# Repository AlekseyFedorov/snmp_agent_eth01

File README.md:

# SNMP Agent на базе WT32-ETH01

Мониторинг серверного помещения по SNMP v2c: температура, протечка воды, открытие дверей, удалённая смена сетевых настроек.

## Возможности

- **Температура** — DS18B20 по 1-Wire, опрос каждые 2 секунды
- **Протечка воды** — Gidrolock WSP через транзисторную развязку
- **Датчики дверей** — 2 геркона (сухой контакт)
- **Светодиодная индикация** — сеть, авария
- **SNMP v2c** — стандартный MIB2 + кастомный enterprise MIB
- **Удалённая смена IP/шлюза/маски** — SNMP SET с валидацией и авто-перезагрузкой
- **Сброс к заводским** — удержание кнопки 5 секунд (стирает NVS)
- **Аппаратный watchdog** — автоматическая перезагрузка при зависании задач

## Список компонентов (BOM)

| Компонент | Количество | Примечание |
|-----------|-----------|------------|
| WT32-ETH01 | 1 | ESP32 + LAN8720 Ethernet |
| DS18B20 | 1 | Датчик температуры, 1-Wire, TO-92 |
| Gidrolock WSP | 1 | Двухпроводный датчик протечки |
| Геркон (магнитоконтактный) | 2 | NO, сухой контакт, для дверей |
| Транзистор NPN 2N3904 | 1 | Развязка датчика протечки |
| Резистор 4.7 кОм | 1 | Подтяжка DS18B20 (VDD ↔ DQ) |
| Резистор 10 кОм | 2 | База транзистора + стягивание базы к GND |
| Резистор 330 Ом | 2 | Токоограничение светодиодов |
| Светодиод зелёный | 1 | Индикатор «Сеть» |
| Светодиод красный | 1 | Индикатор «Авария» |
| Кнопка тактовая | 1 | Сброс настроек (GPIO 5) |
| Блок питания 5V | 1 | Питание платы и датчиков |
| Макетная плата + провода | — | Для сборки |

## Распиновка

| GPIO | Функция | Режим | Примечание |
|------|---------|-------|------------|
| 32 | DS18B20 DQ | INPUT | 1-Wire данные, pull-up 4.7кОм к 3.3V |
| 33 | Gidrolock WSP | INPUT_PULLUP | Через NPN-транзистор (2N3904) |
| 14 | Дверь 1 | INPUT_PULLUP | Геркон: замкнут на GND = закрыта |
| 15 | Дверь 2 | INPUT_PULLUP | Геркон: замкнут на GND = закрыта |
| 2 | LED Сеть | OUTPUT | Через резистор 330Ω |
| 4 | LED Авария | OUTPUT | Через резистор 330Ω |
| 5 | Кнопка сброса | INPUT_PULLUP | Удержание 5 сек = factory reset |
| 16 | CLK 50MHz | OUTPUT | Внешний осциллятор для LAN8720 |

## Логика работы датчиков

### DS18B20 (температура)

Питание 3.3V, данные по 1-Wire на GPIO 32. Между VDD и DQ обязателен резистор 4.7 кОм. Значение публикуется в SNMP как `INTEGER` (температура × 10).

### Gidrolock WSP (протечка)

Датчик питается от 5V. Без воды — ток не течёт, база транзистора (2N3904) притянута к GND резистором 10 кОм, транзистор закрыт, на GPIO 33 — логическая 1 (PULLUP). При протечке вода замыкает контакты, ток через резистор базы 10 кОм открывает транзистор, GPIO замыкается на GND — логический 0.

> [!CAUTION]
> Никогда не подключайте Gidrolock WSP напрямую к GPIO! Напряжение шлейфа 5–24V сожжёт порт. Только через транзистор.

### Герконы (двери)

Дверь закрыта: магнит рядом, геркон замкнут, GPIO → GND = 0. Дверь открыта: геркон разомкнут, GPIO → PULLUP = 1. SNMP возвращает 1 при открытии (тревога).

## Сборка и прошивка

### Требования

- ESP-IDF v5.0+ (протестировано на v6.0.1)
- LWIP с поддержкой SNMP (включается автоматически через компонент `snmp_lwip`)

### Порядок сборки

```bash
git clone https://github.com/AlekseyFedorov/snmp2_agent_eth01.git
cd snmp2_agent_eth01

idf.py set-target esp32
idf.py build
idf.py -p COM3 flash monitor
```

### Заводские параметры

| Параметр | Значение |
|----------|---------|
| IP-адрес | 10.149.130.75 |
| Шлюз | 10.149.130.65 |
| Маска | 255.255.255.224 |
| Flash | 8 MB |
| SNMP Read Community | public |
| SNMP Write Community | private |

> Параметры хранятся в `main/ethernet_app.c` и NVS. После первого запуска сохраняются в NVS. При изменении через SNMP SET устройство перезагружается.

## Структура проекта

```
snmp2_agent_eth01/
├── CMakeLists.txt
├── sdkconfig
├── sdkconfig.defaults
├── dependencies.lock
├── main/
│   ├── CMakeLists.txt
│   ├── idf_component.yml
│   ├── main.c              # SNMP-агент, дерево MIB, задачи FreeRTOS
│   ├── ethernet_app.c/h    # Инициализация Ethernet, статический IP
│   ├── sensors_app.c/h     # Драйверы датчиков (DS18B20, протечка, герконы)
│   └── led_app.c/h         # Светодиодная индикация
└── components/
    └── snmp_lwip/
        ├── CMakeLists.txt   # Сборка SNMP-исходников lwip
        └── idf_component.yml
```

Примечание: SNMP-исходники lwip собираются отдельным компонентом `snmp_lwip`, поскольку в IDF v6 опция `LWIP_SNMP` исключена из Kconfig.

## SNMP-команды

Базовый OID: `.1.3.6.1.4.1.9999.1`

### Чтение (GET)

```bash
# Температура (×10°C)
snmpget -v 2c -c public <IP> .1.3.6.1.4.1.9999.1.1.0

# Протечка (0 — сухо, 1 — тревога)
snmpget -v 2c -c public <IP> .1.3.6.1.4.1.9999.1.6.0

# Дверь 1 (0 — закрыта, 1 — открыта)
snmpget -v 2c -c public <IP> .1.3.6.1.4.1.9999.1.7.0

# Дверь 2
snmpget -v 2c -c public <IP> .1.3.6.1.4.1.9999.1.8.0

# Пройти всё дерево
snmpwalk -v 2c -c public <IP> .1.3.6.1.4.1.9999.1
```

### Запись (SET)

```bash
# Изменение IP/шлюза/маски (одним пакетом):
snmpset -v 2c -c private <IP> \
  .1.3.6.1.4.1.9999.1.10.0 s "10.149.130.80" \
  .1.3.6.1.4.1.9999.1.11.0 s "10.149.130.65" \
  .1.3.6.1.4.1.9999.1.12.0 s "255.255.255.224"
```

После записи устройство перезагрузится через 1 секунду.

### OID-карта

| OID | Тип | Доступ | Описание |
|-----|-----|--------|----------|
| .1.0 | INTEGER | RO | Температура ×10°C |
| .2.0 | GAUGE32 | RO | Свободная heap-память (байт) |
| .3.0 | TIMETICKS | RO | Uptime (×10 мс) |
| .4.0 | GAUGE32 | RO | Использовано heap, % |
| .5.0 | OCTET STRING | RO | MAC-адрес (6 байт) |
| .6.0 | INTEGER | RO | Протечка воды (0 — сухо, 1 — тревога) |
| .7.0 | INTEGER | RO | Дверь 1 (0 — закрыта, 1 — открыта) |
| .8.0 | INTEGER | RO | Дверь 2 (0 — закрыта, 1 — открыта) |
| .10.0 | OCTET STRING | RW | IP-адрес |
| .11.0 | OCTET STRING | RW | Шлюз |
| .12.0 | OCTET STRING | RW | Маска подсети |

## Индикация

| Светодиод | GPIO | Логика |
|-----------|------|--------|
| LED Сеть (зелёный) | IO2 | Горит — сеть активна; мигает — нет линка |
| LED Авария (красный) | IO4 | Мигает при: протечке, открытой двери, t > 45°C |

## Сброс к заводским настройкам

Удержание кнопки на GPIO 5 в течение 5 секунд стирает NVS-раздел. После перезагрузки устройство стартует с параметрами по умолчанию из `ethernet_app.c`.

## Возможные улучшения

- **DHT22 / BME280** — датчик влажности и давления для полного климат-контроля
- **Оптрон PC817** — гальваническая развязка датчика протечки вместо транзистора
- **SNMP Trap** — активная отправка уведомлений в NMS (Zabbix/PRTG) при авариях
- **mDNS** — авто-обнаружение устройства в сети (`snmp-agent.local`)

## Лицензия

MIT.

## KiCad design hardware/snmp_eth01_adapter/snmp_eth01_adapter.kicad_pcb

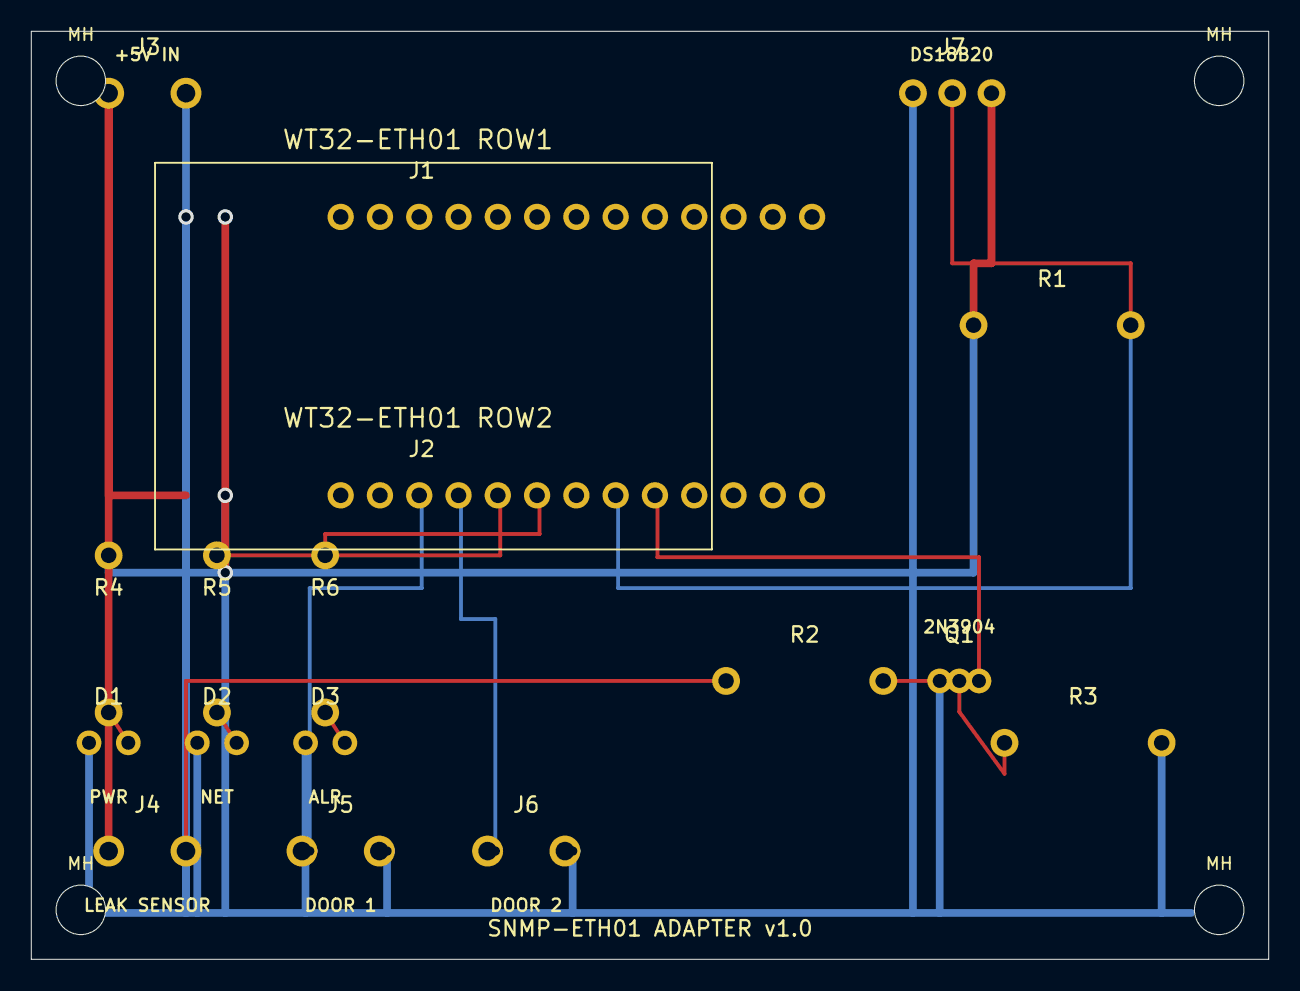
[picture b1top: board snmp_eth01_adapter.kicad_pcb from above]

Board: 2 copper layers, 80.0 x 60.0 mm, 21 parts (0 on the bottom side), 14 nets.

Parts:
D1: LED_PWR; D1
D2: LED_NET; D2
D3: LED_ALR; D3
J1: PinSocket_1x13_2.54mm; J1
J2: PinSocket_1x13_2.54mm; J2
J3: PWR_IN_5V; J3
J4: GIDROLOCK_WSP; J4
J5: DOOR_1; J5
J6: DOOR_2; J6
J7: DS18B20; J7
MH: M3; MountingHole_3.2mm_M3
MH#2, MH#3, MH#4: M3; MountingHole_3.2mm_M3
Q1: 2N3904; Q1
R1: 4.7k; R1
R2: 10k; R2
R3: 10k; R3
R4: 330R; R4
R5: 330R; R5
R6: 330R; R6

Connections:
+3V3: J1.2, J7.3, R1.1, R4.1
+5V: J2.1, J3.1, J4.1
/ALR_LED_A: D3.A, R6.2
/ALR_LED_IO: J2.10, R6.1
/DATA_1WIRE: J2.12, J7.2, R1.2
/DOOR1_IO: J2.7, J5.1
/DOOR2_IO: J2.8, J6.1
/H2O_SIGNAL: J4.2, R2.1
/LEAK_IO: J2.13, Q1.3
/NET_LED_A: D2.A, R5.2
/NET_LED_IO: J2.9, R5.1
/PWR_LED_A: D1.A, R4.2
/TR_BASE: Q1.2, R2.2, R3.1
GND: D1.K, D2.K, D3.K, J1.1, J2.2, J3.2, J5.2, J6.2, J7.1, Q1.1, R3.2

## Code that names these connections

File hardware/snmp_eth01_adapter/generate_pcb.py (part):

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
# ─── NET IDs ──────────────────────────────────────────────
GND = 3;  V5  = 1;  V33 = 2
DQ  = 4   # /DATA_1WIRE   IO32
LEAK= 5   # /LEAK_IO      IO33  (collector of Q1)
H2O = 6   # /H2O_SIGNAL   Gidrolock sensor output (5V side)
BASE= 7   # /TR_BASE      Q1 base node
DR1 = 8   # /DOOR1_IO     IO14
DR2 = 9   # /DOOR2_IO     IO15
NL  = 10  # /NET_LED_IO   IO2
AL  = 11  # /ALR_LED_IO   IO4
PLA = 12  # /PWR_LED_A    anode of D1 (after R4)
NLA = 13  # /NET_LED_A    anode of D2 (after R5)
ALA = 14  # /ALR_LED_A    anode of D3 (after R6)

NET_NAMES = {
    0: "",      1: "+5V",       2: "+3V3",      3: "GND",
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
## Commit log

2026-01-27 Добавлены два OID уникальный номер и загрузка процессора (сильно облегченная)
2026-01-27 Improve readability of SNMP system group details
    Formatted the SNMP system group hierarchy for better readability.
2026-01-27 Update README with system group nodes
    Добавлены основные узлы группы system в документацию.
2026-01-27 Исправление орфографических ошибок
2026-02-26 add .gitignore
2026-02-26 rm sdkconfig
2026-02-26 del sdkconfig
2026-03-01 Add flask size output
2026-03-01 Clear nvs 10 sec
2026-03-12 синхронизация
2026-03-13 Sync
2026-03-13 feat: update ethernet application logic for improved stability and performance
2026-03-13 chore: add .idea to .gitignore and remove a comment
2026-03-14 feat: update default network settings and enhance SNMP configuration
2026-03-22 Исправлена ошибка установки ip адреса, добавлено описание установки сетевых параметров через snmpset
2026-03-22 feat: Add SNMP OID 6 for water leak sensor status.
2026-03-22 docs: Update README with improved information and clarity.
2026-04-14 feat: initialize project structure with system prompt, overview, and sensor application files
2026-04-21 feat: add Fritzing part file for WT32-ETH01 module
2026-04-29 edit fiz
2026-04-29 Refactor code structure for improved readability and maintainability
2026-04-30 docs: add door sensors wiring diagram (Fritzing SVG)
2026-04-30 fix: remove duplicate
2026-05-02 docs: add sensors schematic documentation for snmp_agent_eth01
2026-05-05 fix: remove duplicate entry in .gitignore and update sdkconfig version
2026-05-05 fix: remove duplicate entry in .gitignore and delete dependencies.lock
2026-05-11 feat: implement SNMP agent for network configuration and sensor monitoring with factory reset support
2026-05-11 feat: add Fritzing circuit diagram for snmp_agent_eth01 project
2026-05-11 feat: implement status LED management and expand system configuration via SNMP
2026-05-11 feat: add Fritzing design file for snmp_agent_eth01 hardware schematic
2026-05-15 feat: add sensor application logic, project documentation, and Fritzing hardware diagram
2026-05-15 docs: add chat log for 2026-05-15
2026-05-17 feat: add breadboard wiring diagram SVG and update documentation
2026-05-18 feat: implement SNMP main application logic with sensor polling, network configuration via SNMP, and factory reset functionality
2026-05-28 Changes Antigravity 2.0
2026-05-29 feat: enhance sensor monitoring with door status logging and initialization
2026-06-06 Replaced: transistor -> 2N3904, leak sensor -> Gidrolock WSP.
2026-06-06 Minor edits.
2026-06-06 LWIP_STATS = y
2026-06-13 Stop tracking sdkconfig
2026-06-13 chore: add sdkconfig to gitignore
2026-06-17 refactor: update ethernet configuration, improve sensor polling, and initialize KiCad hardware design files
2026-06-17 feat: add hardware adapter PCB design and update main logic with non-blocking sensor acquisition and robust reboot timer handling
2026-06-19 gitignore: add .deepseek
2026-06-19 feat: add Task Watchdog (TWDT) for all background tasks - 5s timeout triggers panic reset if any task hangs
2026-06-19 build: add esp_system to REQUIRES for esp_task_wdt
2026-06-20 feat: add snmp_lwip component, update docs and build config
